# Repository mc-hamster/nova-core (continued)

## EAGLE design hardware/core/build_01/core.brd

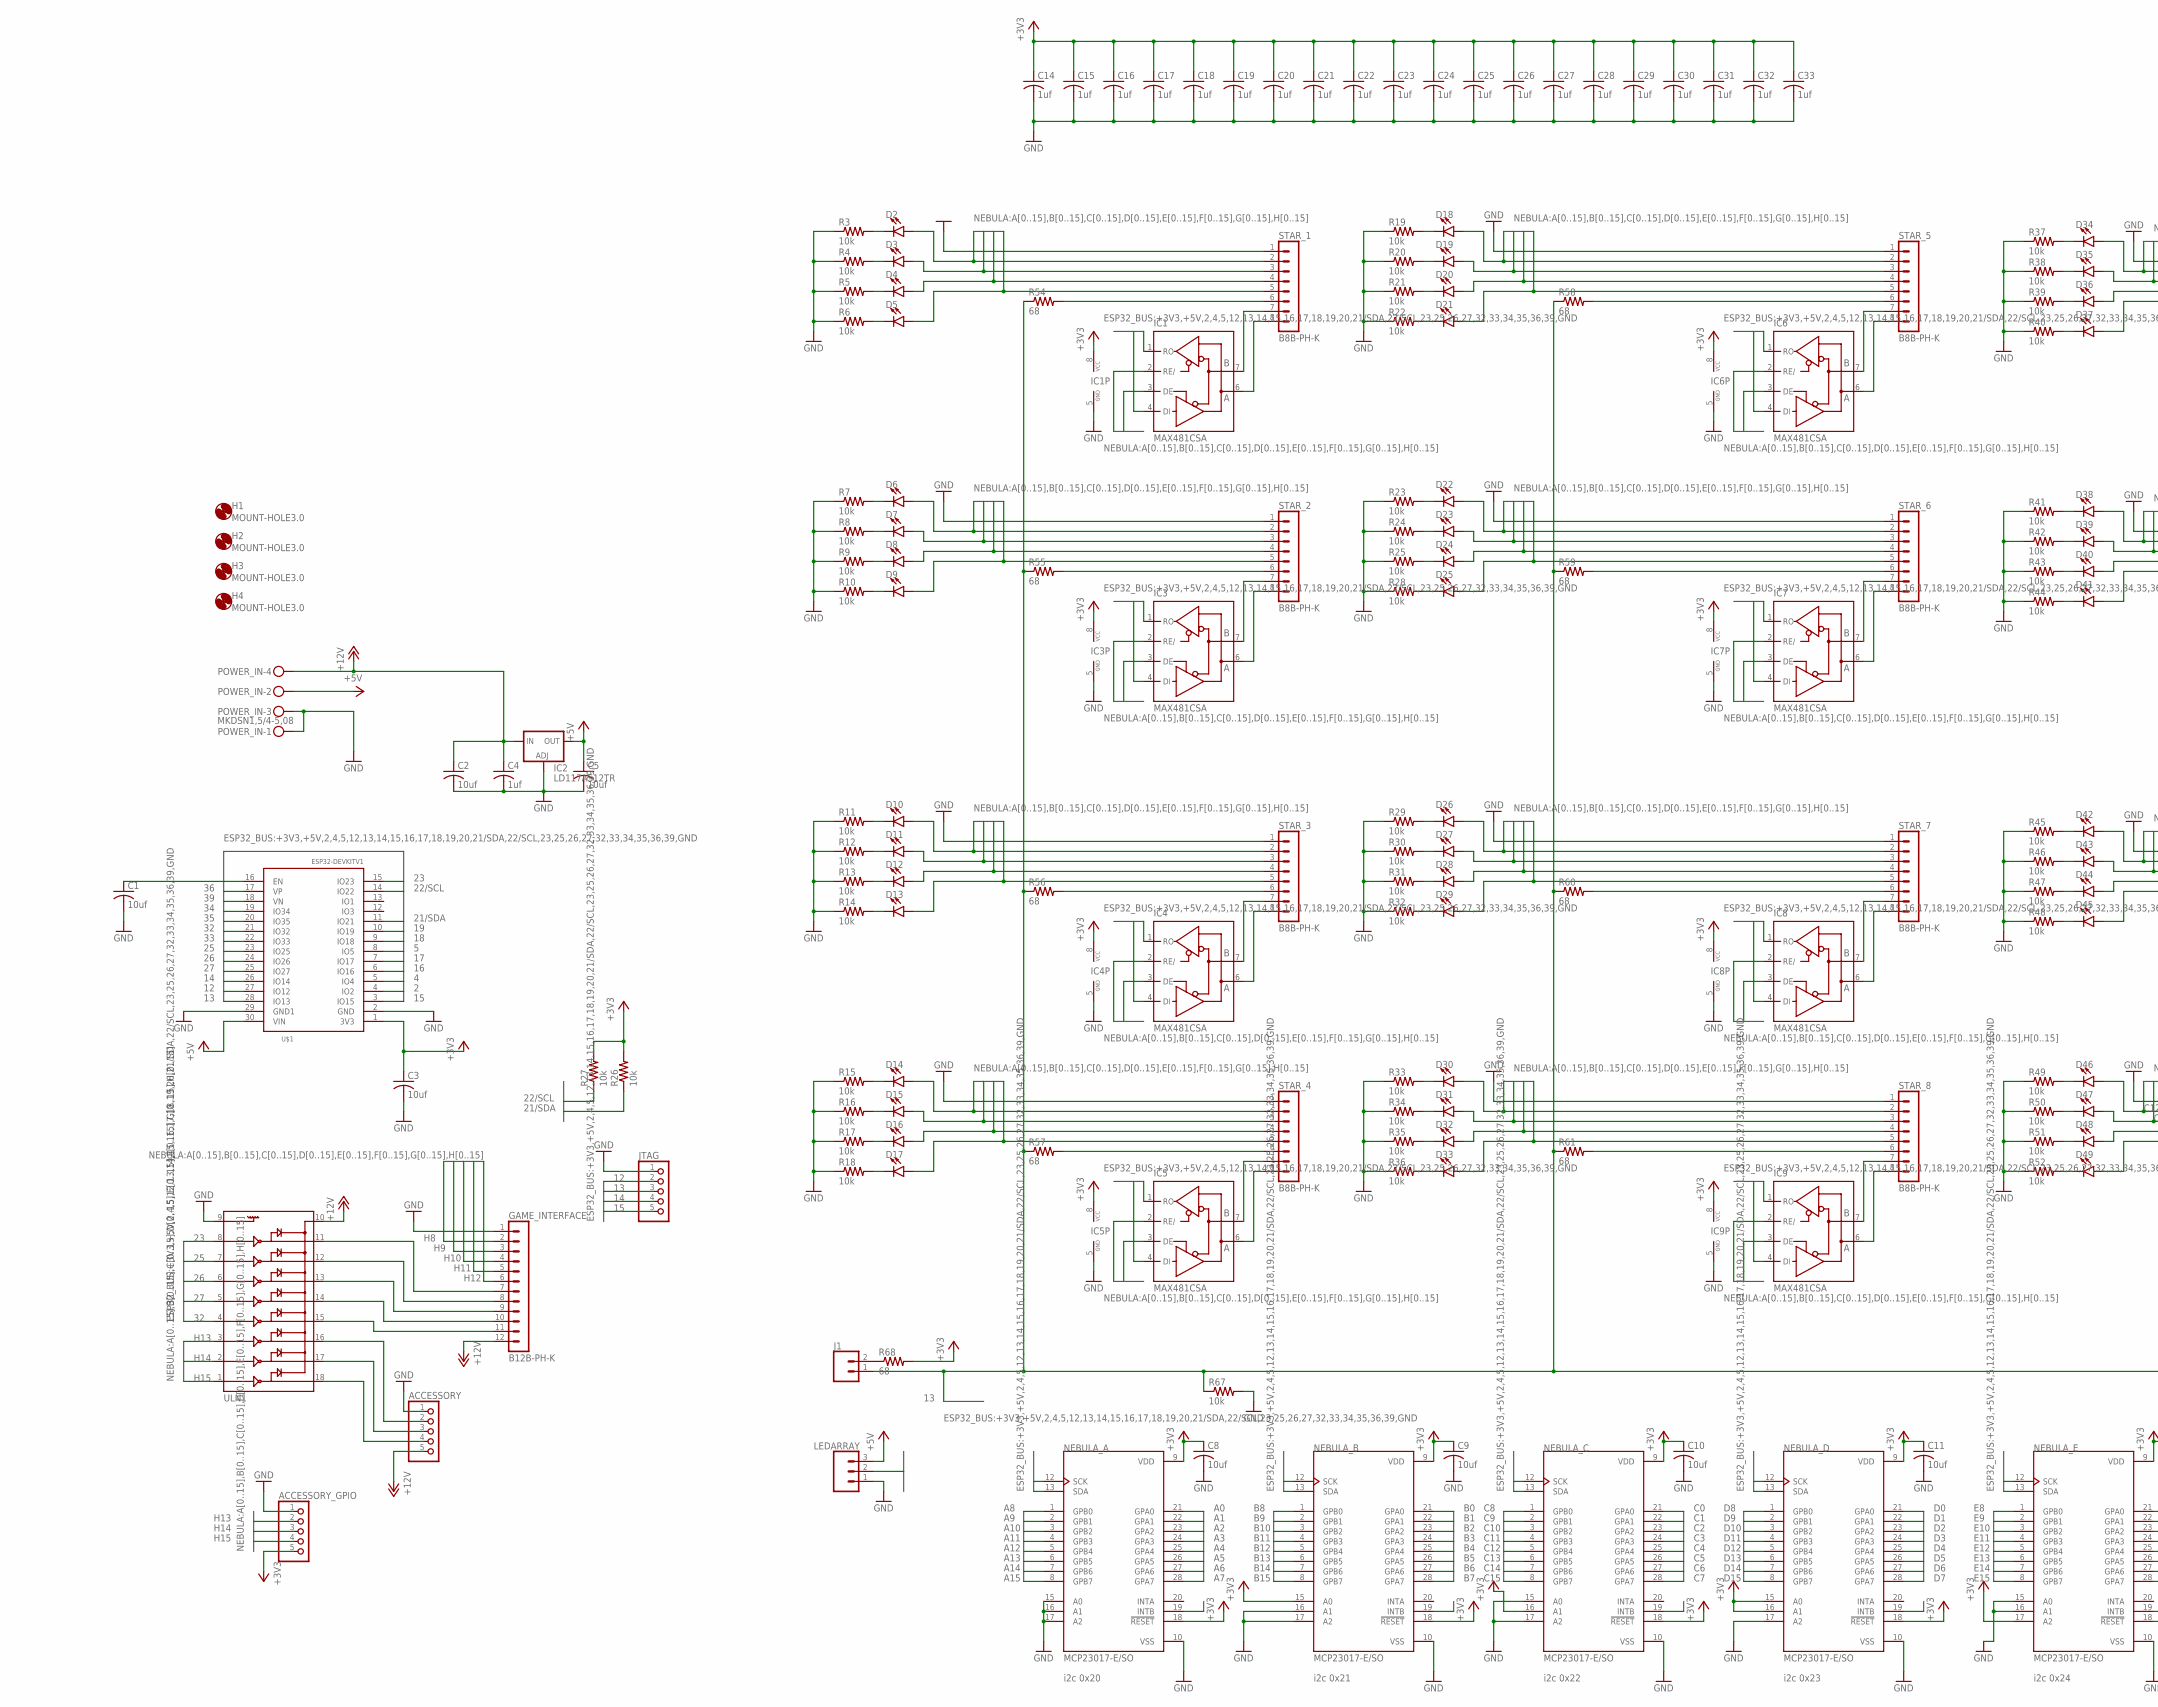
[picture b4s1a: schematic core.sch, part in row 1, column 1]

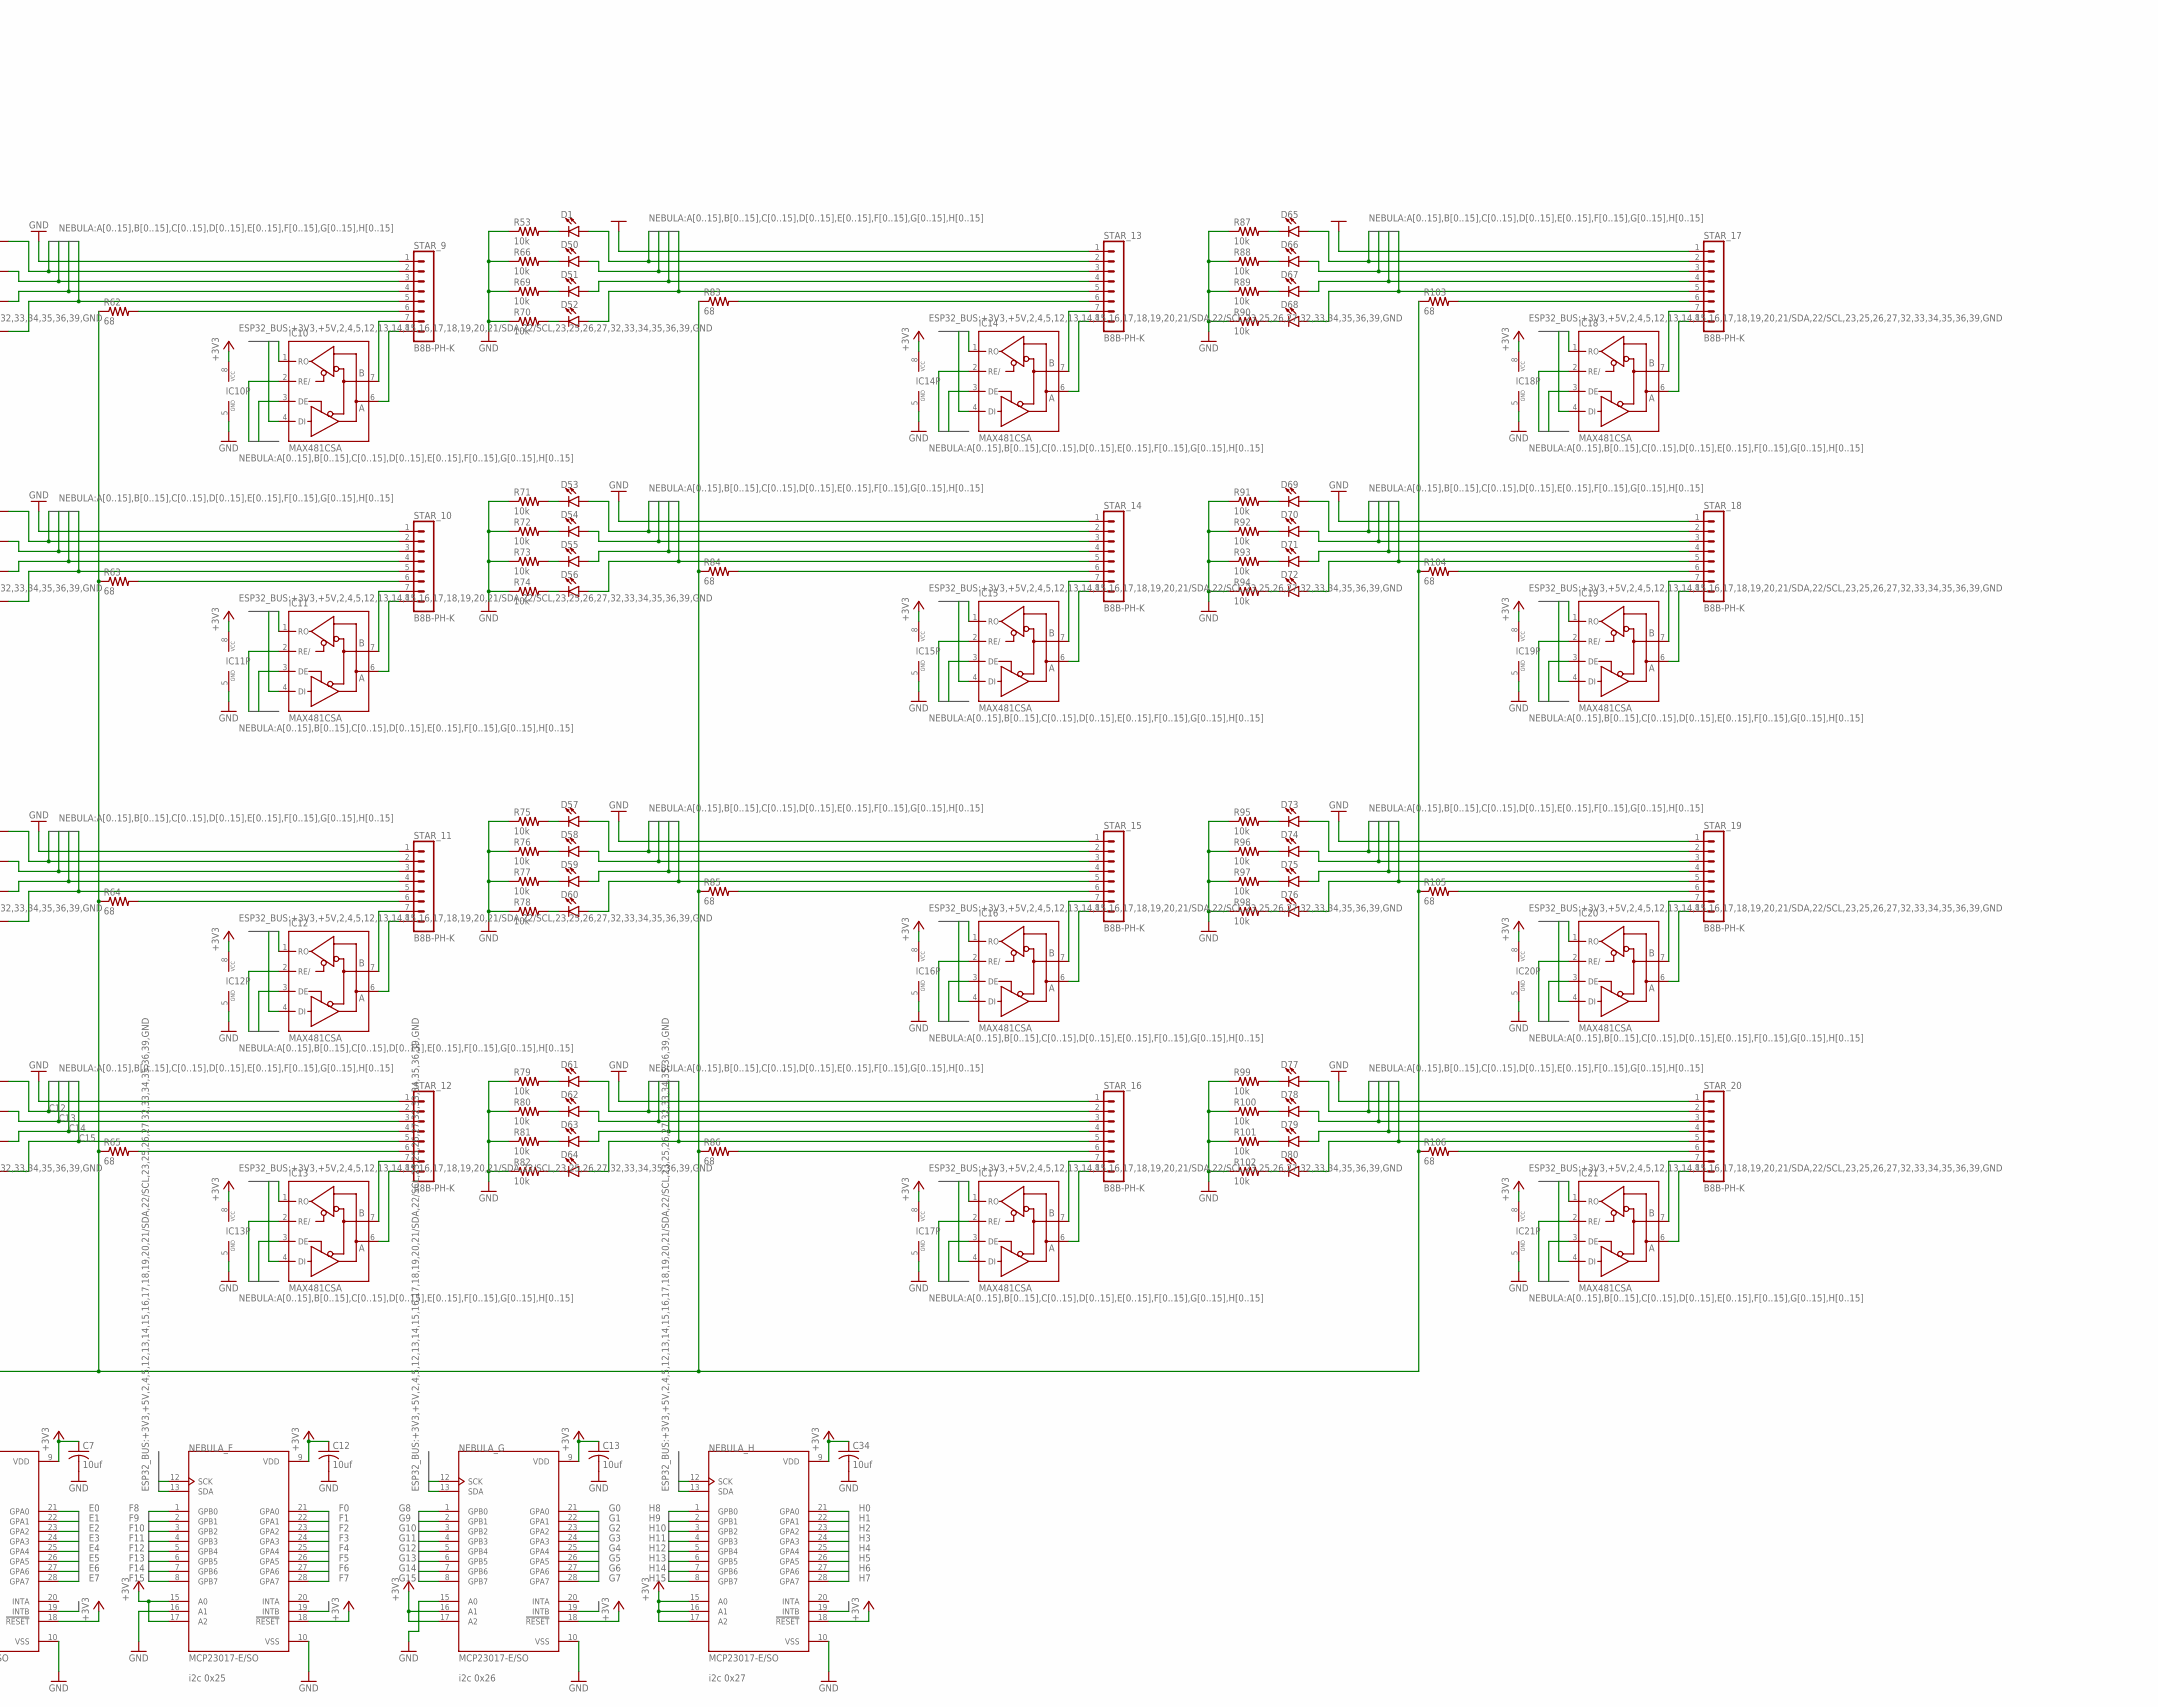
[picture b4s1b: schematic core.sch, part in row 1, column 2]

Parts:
ACCESSORY: PINHD-1X5; 1X05
ACCESSORY_GPIO: PINHD-1X5; 1X05
C1, C2, C3, C5, C7, C8, C9, C10, C11, C12, C13, C34: 10uf; C0603; LCSC_PART C19702
C4, C14, C15, C16, C17, C18, C19, C20, C21, C22, C23, C24, C25, C26, C27, C28, C29, C30, C31, C32, C33: 1uf; C0805; LCSC_PART C15849
D1, D2, D6, D10, D14, D18, D22, D26, D30, D34, D38, D42, D46, D53, D57, D61, D65, D69, D73, D77: LED0603; LED-0603; LCSC_PART C2286
D3, D7, D11, D15, D19, D23, D27, D31, D35, D39, D43, D47, D50, D54, D58, D62, D66, D70, D74, D78: LED0603; LED-0603; LCSC_PART C72043
D4, D8, D12, D16, D20, D24, D28, D32, D36, D40, D44, D48, D51, D55, D59, D63, D67, D71, D75, D79: LED0603; LED-0603; LCSC_PART C72041
D5, D9, D13, D17, D21, D25, D29, D33, D37, D41, D45, D49, D52, D56, D60, D64, D68, D72, D76, D80: LED0603; LED-0603; LCSC_PART C2290
GAME_INTERFACE: B12B-PH-K
H1, H2, H3, H4: MOUNT-HOLE3.0; 3,0
IC1, IC3, IC4, IC5, IC6, IC7, IC8, IC9, IC10, IC11, IC12, IC13, IC14, IC15, IC16, IC17, IC18, IC19, IC20, IC21: MAX481CSA; SO08; LCSC_PART C8963
IC2: LD117AS12TR; SOT223; LCSC_PART C6187
J1: CONN_02JST-PTH-2; JST-2-PTH
JTAG: PINHD-1X5; 1X05
LEDARRAY: CONN_03; 1X03
NEBULA_A: MCP23017-E/SO; SOIC127P1030X265-28N; LCSC_PART C629440
NEBULA_B: MCP23017-E/SO; SOIC127P1030X265-28N; LCSC_PART C629440
NEBULA_C: MCP23017-E/SO; SOIC127P1030X265-28N; LCSC_PART C629440
NEBULA_D: MCP23017-E/SO; SOIC127P1030X265-28N; LCSC_PART C629440
NEBULA_E: MCP23017-E/SO; SOIC127P1030X265-28N; LCSC_PART C629440
NEBULA_F: MCP23017-E/SO; SOIC127P1030X265-28N; LCSC_PART C629440
NEBULA_G: MCP23017-E/SO; SOIC127P1030X265-28N; LCSC_PART C629440
NEBULA_H: MCP23017-E/SO; SOIC127P1030X265-28N; LCSC_PART C629440
POWER_IN: MKDSN1,5/4-5,08
R3, R4, R5, R6, R7, R8, R9, R10, R11, R12, R13, R14, R15, R16, R17, R18, R19, R20, R21, R22, R23, R24, R25, R26, R27, R28, R29, R30, R31, R32, R33, R34, R35, R36, R37, R38, R39, R40, R41, R42, R43, R44, R45, R46, R47, R48, R49, R50, R51, R52, R53, R66, R67, R69, R70, R71, R72, R73, R74, R75, R76, R77, R78, R79, R80, R81, R82, R87, R88, R89, R90, R91, R92, R93, R94, R95, R96, R97, R98, R99, R100, R101, R102: 10k; R0603; LCSC_PART C25804
R54, R55, R56, R57, R58, R59, R60, R61, R62, R63, R64, R65, R68, R83, R84, R85, R86, R103, R104, R105, R106: 68; R0603; LCSC_PART C25804
STAR_1, STAR_2, STAR_3, STAR_4, STAR_5, STAR_6, STAR_7, STAR_8, STAR_9, STAR_10, STAR_11, STAR_12, STAR_13, STAR_14, STAR_15, STAR_16, STAR_17, STAR_18, STAR_19, STAR_20: B8B-PH-K
U$1: ESP32DEVKITV1; ESP32-DEVKITV1
ULN1: ULN2803SOIC; SO018

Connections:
2: U$1.4 (IO2)
4: LEDARRAY.2, U$1.5 (IO4)
5: U$1.8 (IO5)
12: JTAG.2, U$1.27 (IO12)
13: J1.1, JTAG.3, R54.1, R55.1, R56.1, R57.1, R58.1, R59.1, R60.1, R61.1, R62.1, R63.1, R64.1, R65.1, R67.1, R83.1, R84.1, R85.1, R86.1, R103.1, R104.1, R105.1, R106.1, U$1.28 (IO13)
14: JTAG.4, U$1.26 (IO14)
15: JTAG.5, U$1.3 (IO15)
16: IC1.1 (RO), IC3.1 (RO), IC4.1 (RO), IC5.1 (RO), IC6.1 (RO), IC7.1 (RO), IC8.1 (RO), IC9.1 (RO), IC10.1 (RO), IC11.1 (RO), IC12.1 (RO), IC13.1 (RO), IC14.1 (RO), IC15.1 (RO), IC16.1 (RO), IC17.1 (RO), IC18.1 (RO), IC19.1 (RO), IC20.1 (RO), IC21.1 (RO), U$1.6 (IO16)
17: IC1.4 (DI), IC3.4 (DI), IC4.4 (DI), IC5.4 (DI), IC6.4 (DI), IC7.4 (DI), IC8.4 (DI), IC9.4 (DI), IC10.4 (DI), IC11.4 (DI), IC12.4 (DI), IC13.4 (DI), IC14.4 (DI), IC15.4 (DI), IC16.4 (DI), IC17.4 (DI), IC18.4 (DI), IC19.4 (DI), IC20.4 (DI), IC21.4 (DI), U$1.7 (IO17)
18: NEBULA_E.19 (INTB), U$1.9 (IO18)
19: NEBULA_F.19 (INTB), U$1.10 (IO19)
21/SDA: NEBULA_A.13 (SDA), NEBULA_B.13 (SDA), NEBULA_C.13 (SDA), NEBULA_D.13 (SDA), NEBULA_E.13 (SDA), NEBULA_F.13 (SDA), NEBULA_G.13 (SDA), NEBULA_H.13 (SDA), R26.1, U$1.11 (IO21)
22/SCL: NEBULA_A.12 (SCK), NEBULA_B.12 (SCK), NEBULA_C.12 (SCK), NEBULA_D.12 (SCK), NEBULA_E.12 (SCK), NEBULA_F.12 (SCK), NEBULA_G.12 (SCK), NEBULA_H.12 (SCK), R27.1, U$1.14 (IO22)
23: U$1.15 (IO23), ULN1.8
25: U$1.23 (IO25), ULN1.7
26: U$1.24 (IO26), ULN1.6
27: U$1.25 (IO27), ULN1.5
32: U$1.21 (IO32), ULN1.4
33: NEBULA_G.19 (INTB), NEBULA_H.19 (INTB), U$1.22 (IO33)
34: NEBULA_A.19 (INTB), U$1.19 (IO34)
35: NEBULA_B.19 (INTB), U$1.20 (IO35)
36: NEBULA_C.19 (INTB), U$1.17 (VP)
39: NEBULA_D.19 (INTB), U$1.18 (VN)
+3V3: ACCESSORY_GPIO.5, C3.1, C7.1, C8.1, C9.1, C10.1, C11.1, C12.1, C13.1, C14.1, C15.1, C16.1, C17.1, C18.1, C19.1, C20.1, C21.1, C22.1, C23.1, C24.1, C25.1, C26.1, C27.1, C28.1, C29.1, C30.1, C31.1, C32.1, C33.1, C34.1, IC1.8 (VCC), IC3.8 (VCC), IC4.8 (VCC), IC5.8 (VCC), IC6.8 (VCC), IC7.8 (VCC), IC8.8 (VCC), IC9.8 (VCC), IC10.8 (VCC), IC11.8 (VCC), IC12.8 (VCC), IC13.8 (VCC), IC14.8 (VCC), IC15.8 (VCC), IC16.8 (VCC), IC17.8 (VCC), IC18.8 (VCC), IC19.8 (VCC), IC20.8 (VCC), IC21.8 (VCC), NEBULA_A.9 (VDD), NEBULA_A.18 (!RESET), NEBULA_B.9 (VDD), NEBULA_B.15 (A0), NEBULA_B.18 (!RESET), NEBULA_C.9 (VDD), NEBULA_C.16 (A1), NEBULA_C.18 (!RESET), NEBULA_D.9 (VDD), NEBULA_D.15 (A0), NEBULA_D.16 (A1), NEBULA_D.18 (!RESET), NEBULA_E.9 (VDD), NEBULA_E.17 (A2), NEBULA_E.18 (!RESET), NEBULA_F.9 (VDD), NEBULA_F.15 (A0), NEBULA_F.17 (A2), NEBULA_F.18 (!RESET), NEBULA_G.9 (VDD), NEBULA_G.16 (A1), NEBULA_G.17 (A2), NEBULA_G.18 (!RESET), NEBULA_H.9 (VDD), NEBULA_H.15 (A0), NEBULA_H.16 (A1), NEBULA_H.17 (A2), NEBULA_H.18 (!RESET), R26.2, R27.2, R68.2, U$1.1 (3V3)
+5V: C5.1, IC2.4 (OUT), LEDARRAY.3, POWER_IN.2, U$1.30 (VIN)
+12V: ACCESSORY.5, C2.1, C4.1, GAME_INTERFACE.12, IC2.3 (IN), POWER_IN.4, ULN1.10
A0: D2.A, NEBULA_A.21 (GPA0), STAR_1.2
A1: D3.A, NEBULA_A.22 (GPA1), STAR_1.3
A2: D4.A, NEBULA_A.23 (GPA2), STAR_1.4
A3: D5.A, NEBULA_A.24 (GPA3), STAR_1.5
A4: D6.A, NEBULA_A.25 (GPA4), STAR_2.2
A5: D7.A, NEBULA_A.26 (GPA5), STAR_2.3
A6: D8.A, NEBULA_A.27 (GPA6), STAR_2.4
A7: D9.A, NEBULA_A.28 (GPA7), STAR_2.5
A8: D10.A, NEBULA_A.1 (GPB0), STAR_3.2
A9: D11.A, NEBULA_A.2 (GPB1), STAR_3.3
A10: D12.A, NEBULA_A.3 (GPB2), STAR_3.4
A11: D13.A, NEBULA_A.4 (GPB3), STAR_3.5
A12: D14.A, NEBULA_A.5 (GPB4), STAR_4.2
A13: D15.A, NEBULA_A.6 (GPB5), STAR_4.3
A14: D16.A, NEBULA_A.7 (GPB6), STAR_4.4
A15: D17.A, NEBULA_A.8 (GPB7), STAR_4.5
B0: D18.A, NEBULA_B.21 (GPA0), STAR_5.2
B1: D19.A, NEBULA_B.22 (GPA1), STAR_5.3
B2: D20.A, NEBULA_B.23 (GPA2), STAR_5.4
B3: D21.A, NEBULA_B.24 (GPA3), STAR_5.5
B4: D22.A, NEBULA_B.25 (GPA4), STAR_6.2
B5: D23.A, NEBULA_B.26 (GPA5), STAR_6.3
B6: D24.A, NEBULA_B.27 (GPA6), STAR_6.4
B7: D25.A, NEBULA_B.28 (GPA7), STAR_6.5
B8: D26.A, NEBULA_B.1 (GPB0), STAR_7.2
B9: D27.A, NEBULA_B.2 (GPB1), STAR_7.3
B10: D28.A, NEBULA_B.3 (GPB2), STAR_7.4
B11: D29.A, NEBULA_B.4 (GPB3), STAR_7.5
B12: D30.A, NEBULA_B.5 (GPB4), STAR_8.2
B13: D31.A, NEBULA_B.6 (GPB5), STAR_8.3
B14: D32.A, NEBULA_B.7 (GPB6), STAR_8.4
B15: D33.A, NEBULA_B.8 (GPB7), STAR_8.5
C0: D34.A, NEBULA_C.21 (GPA0), STAR_9.2
C1: D35.A, NEBULA_C.22 (GPA1), STAR_9.3
C2: D36.A, NEBULA_C.23 (GPA2), STAR_9.4
C3: D37.A, NEBULA_C.24 (GPA3), STAR_9.5
C4: D38.A, NEBULA_C.25 (GPA4), STAR_10.2
C5: D39.A, NEBULA_C.26 (GPA5), STAR_10.3
C6: D40.A, NEBULA_C.27 (GPA6), STAR_10.4
C7: D41.A, NEBULA_C.28 (GPA7), STAR_10.5
C8: D42.A, NEBULA_C.1 (GPB0), STAR_11.2
C9: D43.A, NEBULA_C.2 (GPB1), STAR_11.3
C10: D44.A, NEBULA_C.3 (GPB2), STAR_11.4
C11: D45.A, NEBULA_C.4 (GPB3), STAR_11.5
C12: D46.A, NEBULA_C.5 (GPB4), STAR_12.2
C13: D47.A, NEBULA_C.6 (GPB5), STAR_12.3
C14: D48.A, NEBULA_C.7 (GPB6), STAR_12.4
C15: D49.A, NEBULA_C.8 (GPB7), STAR_12.5
D0: D1.A, NEBULA_D.21 (GPA0), STAR_13.2
D1: D50.A, NEBULA_D.22 (GPA1), STAR_13.3
D2: D51.A, NEBULA_D.23 (GPA2), STAR_13.4
D3: D52.A, NEBULA_D.24 (GPA3), STAR_13.5
D4: D53.A, NEBULA_D.25 (GPA4), STAR_14.2
D5: D54.A, NEBULA_D.26 (GPA5), STAR_14.3
D6: D55.A, NEBULA_D.27 (GPA6), STAR_14.4
D7: D56.A, NEBULA_D.28 (GPA7), STAR_14.5
D8: D57.A, NEBULA_D.1 (GPB0), STAR_15.2
D9: D58.A, NEBULA_D.2 (GPB1), STAR_15.3
D10: D59.A, NEBULA_D.3 (GPB2), STAR_15.4
D11: D60.A, NEBULA_D.4 (GPB3), STAR_15.5
D12: D61.A, NEBULA_D.5 (GPB4), STAR_16.2
D13: D62.A, NEBULA_D.6 (GPB5), STAR_16.3
D14: D63.A, NEBULA_D.7 (GPB6), STAR_16.4
D15: D64.A, NEBULA_D.8 (GPB7), STAR_16.5
E0: D65.A, NEBULA_E.21 (GPA0), STAR_17.2
E1: D66.A, NEBULA_E.22 (GPA1), STAR_17.3
E2: D67.A, NEBULA_E.23 (GPA2), STAR_17.4
E3: D68.A, NEBULA_E.24 (GPA3), STAR_17.5
E4: D69.A, NEBULA_E.25 (GPA4), STAR_18.2
E5: D70.A, NEBULA_E.26 (GPA5), STAR_18.3
E6: D71.A, NEBULA_E.27 (GPA6), STAR_18.4
E7: D72.A, NEBULA_E.28 (GPA7), STAR_18.5
E8: D73.A, NEBULA_E.1 (GPB0), STAR_19.2
E9: D74.A, NEBULA_E.2 (GPB1), STAR_19.3
E10: D75.A, NEBULA_E.3 (GPB2), STAR_19.4
E11: D76.A, NEBULA_E.4 (GPB3), STAR_19.5
E12: D77.A, NEBULA_E.5 (GPB4), STAR_20.2
E13: D78.A, NEBULA_E.6 (GPB5), STAR_20.3
E14: D79.A, NEBULA_E.7 (GPB6), STAR_20.4
E15: D80.A, NEBULA_E.8 (GPB7), STAR_20.5
F0: IC1.2 (RE/), NEBULA_F.21 (GPA0)
F1: IC1.3 (DE), NEBULA_F.22 (GPA1)
F2: IC3.2 (RE/), NEBULA_F.23 (GPA2)
F3: IC3.3 (DE), NEBULA_F.24 (GPA3)
F4: IC4.2 (RE/), NEBULA_F.25 (GPA4)
F5: IC4.3 (DE), NEBULA_F.26 (GPA5)
F6: IC5.2 (RE/), NEBULA_F.27 (GPA6)
F7: IC5.3 (DE), NEBULA_F.28 (GPA7)
F8: IC6.2 (RE/), NEBULA_F.1 (GPB0)
F9: IC6.3 (DE), NEBULA_F.2 (GPB1)
F10: IC7.2 (RE/), NEBULA_F.3 (GPB2)
F11: IC7.3 (DE), NEBULA_F.4 (GPB3)
F12: IC8.2 (RE/), NEBULA_F.5 (GPB4)
F13: IC8.3 (DE), NEBULA_F.6 (GPB5)
F14: IC9.2 (RE/), NEBULA_F.7 (GPB6)
F15: IC9.3 (DE), NEBULA_F.8 (GPB7)
G0: IC10.2 (RE/), NEBULA_G.21 (GPA0)
G1: IC10.3 (DE), NEBULA_G.22 (GPA1)
G2: IC11.2 (RE/), NEBULA_G.23 (GPA2)
G3: IC11.3 (DE), NEBULA_G.24 (GPA3)
G4: IC12.2 (RE/), NEBULA_G.25 (GPA4)
G5: IC12.3 (DE), NEBULA_G.26 (GPA5)
G6: IC13.2 (RE/), NEBULA_G.27 (GPA6)
G7: IC13.3 (DE), NEBULA_G.28 (GPA7)
G8: IC14.2 (RE/), NEBULA_G.1 (GPB0)
G9: IC14.3 (DE), NEBULA_G.2 (GPB1)
G10: IC15.2 (RE/), NEBULA_G.3 (GPB2)
G11: IC15.3 (DE), NEBULA_G.4 (GPB3)
G12: IC16.2 (RE/), NEBULA_G.5 (GPB4)
G13: IC16.3 (DE), NEBULA_G.6 (GPB5)
G14: IC17.2 (RE/), NEBULA_G.7 (GPB6)
G15: IC17.3 (DE), NEBULA_G.8 (GPB7)
GND: ACCESSORY.1, ACCESSORY_GPIO.1, C1.2, C2.2, C3.2, C4.2, C5.2, C7.2, C8.2, C9.2, C10.2, C11.2, C12.2, C13.2, C14.2, C15.2, C16.2, C17.2, C18.2, C19.2, C20.2, C21.2, C22.2, C23.2, C24.2, C25.2, C26.2, C27.2, C28.2, C29.2, C30.2, C31.2, C32.2, C33.2, C34.2, GAME_INTERFACE.1, IC1.5 (GND), IC2.1 (ADJ), IC3.5 (GND), IC4.5 (GND), IC5.5 (GND), IC6.5 (GND), IC7.5 (GND), IC8.5 (GND), IC9.5 (GND), IC10.5 (GND), IC11.5 (GND), IC12.5 (GND), IC13.5 (GND), IC14.5 (GND), IC15.5 (GND), IC16.5 (GND), IC17.5 (GND), IC18.5 (GND), IC19.5 (GND), IC20.5 (GND), IC21.5 (GND), JTAG.1, LEDARRAY.1, NEBULA_A.10 (VSS), NEBULA_A.15 (A0), NEBULA_A.16 (A1), NEBULA_A.17 (A2), NEBULA_B.10 (VSS), NEBULA_B.16 (A1), NEBULA_B.17 (A2), NEBULA_C.10 (VSS), NEBULA_C.15 (A0), NEBULA_C.17 (A2), NEBULA_D.10 (VSS), NEBULA_D.17 (A2), NEBULA_E.10 (VSS), NEBULA_E.15 (A0), NEBULA_E.16 (A1), NEBULA_F.10 (VSS), NEBULA_F.16 (A1), NEBULA_G.10 (VSS), NEBULA_G.15 (A0), NEBULA_H.10 (VSS), POWER_IN.1, POWER_IN.3, R3.1, R4.1, R5.1, R6.1, R7.1, R8.1, R9.1, R10.1, R11.1, R12.1, R13.1, R14.1, R15.1, R16.1, R17.1, R18.1, R19.1, R20.1, R21.1, R22.1, R23.1, R24.1, R25.1, R28.1, R29.1, R30.1, R31.1, R32.1, R33.1, R34.1, R35.1, R36.1, R37.1, R38.1, R39.1, R40.1, R41.1, R42.1, R43.1, R44.1, R45.1, R46.1, R47.1, R48.1, R49.1, R50.1, R51.1, R52.1, R53.1, R66.1, R67.2, R69.1, R70.1, R71.1, R72.1, R73.1, R74.1, R75.1, R76.1, R77.1, R78.1, R79.1, R80.1, R81.1, R82.1, R87.1, R88.1, R89.1, R90.1, R91.1, R92.1, R93.1, R94.1, R95.1, R96.1, R97.1, R98.1, R99.1, R100.1, R101.1, R102.1, STAR_1.1, STAR_2.1, STAR_3.1, STAR_4.1, STAR_5.1, STAR_6.1, STAR_7.1, STAR_8.1, STAR_9.1, STAR_10.1, STAR_11.1, STAR_12.1, STAR_13.1, STAR_14.1, STAR_15.1, STAR_16.1, STAR_17.1, STAR_18.1, STAR_19.1, STAR_20.1, U$1.2 (GND), U$1.29 (GND1), ULN1.9
H0: IC18.2 (RE/), NEBULA_H.21 (GPA0)
H1: IC18.3 (DE), NEBULA_H.22 (GPA1)
H2: IC19.2 (RE/), NEBULA_H.23 (GPA2)
H3: IC19.3 (DE), NEBULA_H.24 (GPA3)
H4: IC20.2 (RE/), NEBULA_H.25 (GPA4)
H5: IC20.3 (DE), NEBULA_H.26 (GPA5)
H6: IC21.2 (RE/), NEBULA_H.27 (GPA6)
H7: IC21.3 (DE), NEBULA_H.28 (GPA7)
H8: GAME_INTERFACE.2, NEBULA_H.1 (GPB0)
H9: GAME_INTERFACE.3, NEBULA_H.2 (GPB1)
H10: GAME_INTERFACE.4, NEBULA_H.3 (GPB2)
H11: GAME_INTERFACE.5, NEBULA_H.4 (GPB3)
H12: GAME_INTERFACE.6, NEBULA_H.5 (GPB4)
H13: ACCESSORY_GPIO.2, NEBULA_H.6 (GPB5), ULN1.3
H14: ACCESSORY_GPIO.3, NEBULA_H.7 (GPB6), ULN1.2
H15: ACCESSORY_GPIO.4, NEBULA_H.8 (GPB7), ULN1.1
unnamed: C1.1, U$1.16 (EN)
unnamed: R55.2, STAR_2.6
unnamed: D2.C, R3.2
unnamed: D3.C, R4.2
unnamed: D4.C, R5.2
unnamed: D5.C, R6.2
unnamed: R56.2, STAR_3.6
unnamed: R57.2, STAR_4.6
unnamed: R54.2, STAR_1.6
unnamed: R58.2, STAR_5.6
unnamed: D6.C, R7.2
unnamed: D7.C, R8.2
unnamed: D8.C, R9.2
unnamed: D9.C, R10.2
unnamed: R59.2, STAR_6.6
unnamed: R60.2, STAR_7.6
unnamed: R61.2, STAR_8.6
unnamed: R65.2, STAR_12.6
unnamed: R64.2, STAR_11.6
unnamed: D10.C, R11.2
unnamed: D11.C, R12.2
unnamed: D12.C, R13.2
unnamed: D13.C, R14.2
unnamed: R63.2, STAR_10.6
unnamed: R62.2, STAR_9.6
unnamed: D1.C, R53.2
unnamed: D50.C, R66.2
unnamed: D14.C, R15.2
unnamed: D15.C, R16.2
unnamed: D16.C, R17.2
unnamed: D17.C, R18.2
unnamed: D51.C, R69.2
unnamed: D52.C, R70.2
unnamed: D65.C, R87.2
unnamed: D53.C, R71.2
unnamed: D18.C, R19.2
unnamed: D19.C, R20.2
unnamed: D20.C, R21.2
unnamed: D21.C, R22.2
unnamed: D54.C, R72.2
unnamed: D55.C, R73.2
unnamed: D56.C, R74.2
unnamed: D57.C, R75.2
unnamed: D22.C, R23.2
unnamed: D23.C, R24.2
unnamed: D24.C, R25.2
unnamed: D25.C, R28.2
unnamed: D58.C, R76.2
unnamed: D59.C, R77.2
unnamed: D60.C, R78.2
unnamed: GAME_INTERFACE.7, ULN1.11
unnamed: D26.C, R29.2
unnamed: D27.C, R30.2
unnamed: D28.C, R31.2
unnamed: D29.C, R32.2
unnamed: GAME_INTERFACE.8, ULN1.12
unnamed: GAME_INTERFACE.9, ULN1.13
unnamed: GAME_INTERFACE.10, ULN1.14
unnamed: GAME_INTERFACE.11, ULN1.15
unnamed: D30.C, R33.2
unnamed: D31.C, R34.2
unnamed: D32.C, R35.2
unnamed: D33.C, R36.2
unnamed: D61.C, R79.2
unnamed: D62.C, R80.2
unnamed: D63.C, R81.2
unnamed: D64.C, R82.2
unnamed: D34.C, R37.2
unnamed: D35.C, R38.2
unnamed: D36.C, R39.2
unnamed: D37.C, R40.2
unnamed: R84.2, STAR_14.6
unnamed: R85.2, STAR_15.6
unnamed: R86.2, STAR_16.6
unnamed: R83.2, STAR_13.6
unnamed: D38.C, R41.2
unnamed: D39.C, R42.2
unnamed: D40.C, R43.2
unnamed: D41.C, R44.2
unnamed: D66.C, R88.2
unnamed: D67.C, R89.2
unnamed: D68.C, R90.2
unnamed: D69.C, R91.2
unnamed: D42.C, R45.2
unnamed: D43.C, R46.2
unnamed: D44.C, R47.2
unnamed: D45.C, R48.2
unnamed: D70.C, R92.2
unnamed: J1.2, R68.1
unnamed: D71.C, R93.2
unnamed: D72.C, R94.2
unnamed: D73.C, R95.2
unnamed: D46.C, R49.2
unnamed: D47.C, R50.2
unnamed: D48.C, R51.2
unnamed: D49.C, R52.2
unnamed: D74.C, R96.2
unnamed: D75.C, R97.2
unnamed: D76.C, R98.2
unnamed: D77.C, R99.2
unnamed: D78.C, R100.2
unnamed: D79.C, R101.2
unnamed: D80.C, R102.2
unnamed: R104.2, STAR_18.6
unnamed: R105.2, STAR_19.6
unnamed: R106.2, STAR_20.6
unnamed: R103.2, STAR_17.6
unnamed: IC1.7 (B), STAR_1.7
unnamed: IC1.6 (A), STAR_1.8
unnamed: IC3.7 (B), STAR_2.7
unnamed: IC3.6 (A), STAR_2.8
unnamed: IC4.7 (B), STAR_3.7
unnamed: IC4.6 (A), STAR_3.8
unnamed: IC5.7 (B), STAR_4.7
unnamed: IC5.6 (A), STAR_4.8
unnamed: IC6.7 (B), STAR_5.7
unnamed: IC6.6 (A), STAR_5.8
unnamed: IC7.7 (B), STAR_6.7
unnamed: IC7.6 (A), STAR_6.8
unnamed: IC8.7 (B), STAR_7.7
unnamed: IC8.6 (A), STAR_7.8
unnamed: IC9.7 (B), STAR_8.7
unnamed: IC9.6 (A), STAR_8.8
unnamed: IC10.7 (B), STAR_9.7
unnamed: IC10.6 (A), STAR_9.8
unnamed: IC11.7 (B), STAR_10.7
unnamed: IC11.6 (A), STAR_10.8
unnamed: IC12.7 (B), STAR_11.7
unnamed: IC12.6 (A), STAR_11.8
unnamed: IC13.7 (B), STAR_12.7
unnamed: IC13.6 (A), STAR_12.8
unnamed: IC14.7 (B), STAR_13.7
unnamed: IC14.6 (A), STAR_13.8
unnamed: IC15.7 (B), STAR_14.7
unnamed: IC15.6 (A), STAR_14.8
unnamed: IC16.7 (B), STAR_15.7
unnamed: IC16.6 (A), STAR_15.8
unnamed: IC17.7 (B), STAR_16.7
unnamed: IC17.6 (A), STAR_16.8
unnamed: IC18.7 (B), STAR_17.7
unnamed: IC18.6 (A), STAR_17.8
unnamed: IC19.7 (B), STAR_18.7
unnamed: IC19.6 (A), STAR_18.8
unnamed: IC20.7 (B), STAR_19.7
unnamed: IC20.6 (A), STAR_19.8
unnamed: IC21.7 (B), STAR_20.7
unnamed: IC21.6 (A), STAR_20.8
unnamed: ACCESSORY.2, ULN1.16
unnamed: ACCESSORY.3, ULN1.17
unnamed: ACCESSORY.4, ULN1.18

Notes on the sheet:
i2c 0x20
i2c 0x21
i2c 0x22
i2c 0x23
i2c 0x24
i2c 0x25
i2c 0x26
i2c 0x27

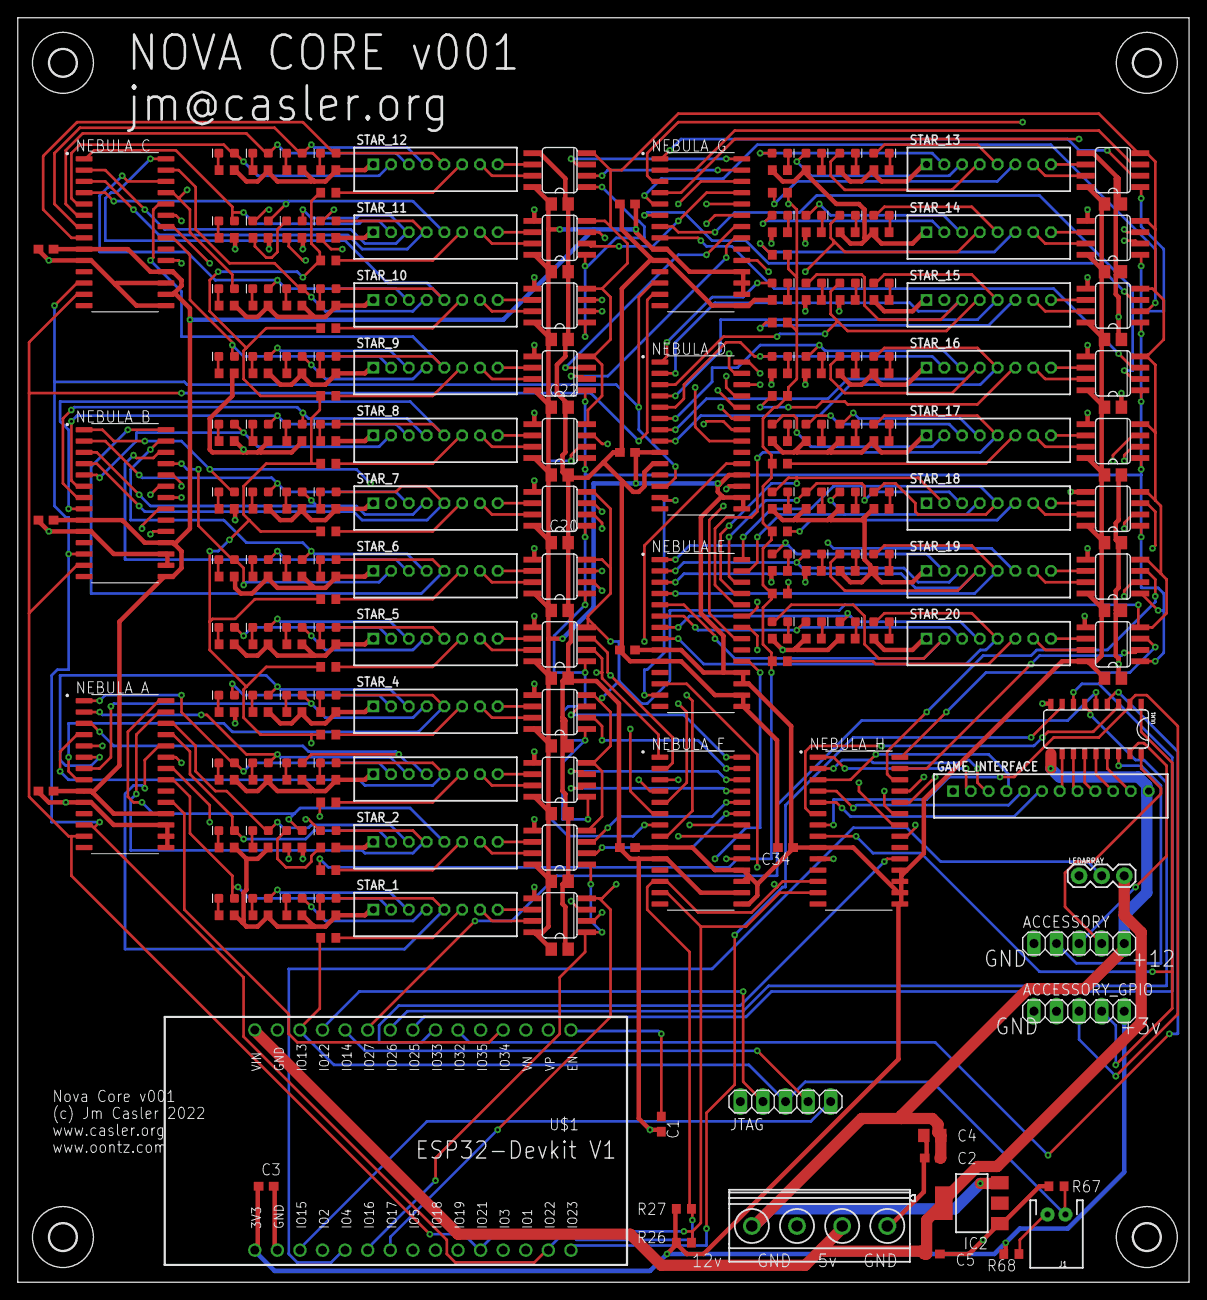
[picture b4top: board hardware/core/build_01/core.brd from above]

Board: 4 copper layers, 131.8 x 142.2 mm, 279 parts (0 on the bottom side), 303 nets.

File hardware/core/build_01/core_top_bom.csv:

Comment,Designator,Footprint,LCSC Part #
1uf,D1 D2 D3 D4 D5 D6 D7 D8 D9 D10 D11 D12 D13 D14 D15 D16 D17 D18 D19 D20 D21 D22 D23 D24 D25 D26 D27 D28 D29 D30 D31 D32 D33 D34 D35 D36 D37 D38 D39 D40 D41 D42 D43 D44 D45 D46 D47 D48 D49 D50 D51 D52 D53 D54 D55 D56 D57 D58 D59 D60 D61 D62 D63 D64 D65 D66 D67 D68 D69 D70 D71 D72 D73 D74 D75 D76 D77 D78 D79 D80 ULN1 C4 C14 C15 C16 C17 C18 C19 C20 C21 C22 C23 C24 C25 C26 C27 C28 C29 C30 C31 C32 C33,C0805,C15849
10k,R3 R4 R5 R6 R7 R8 R9 R10 R11 R12 R13 R14 R15 R16 R17 R18 R19 R20 R21 R22 R23 R24 R25 R26 R27 R28 R29 R30 R31 R32 R33 R34 R35 R36 R37 R38 R39 R40 R41 R42 R43 R44 R45 R46 R47 R48 R49 R50 R51 R52 R53 R66 R67 R69 R70 R71 R72 R73 R74 R75 R76 R77 R78 R79 R80 R81 R82 R87 R88 R89 R90 R91 R92 R93 R94 R95 R96 R97 R98 R99 R100 R101 R102,R0603,C25804
10uf,C1 C2 C3 C5 C7 C8 C9 C10 C11 C12 C13 C34,C0603,C19702
68,R54 R55 R56 R57 R58 R59 R60 R61 R62 R63 R64 R65 R68 R83 R84 R85 R86 R103 R104 R105 R106,R0603,C25804
LD117AS12TR,IC2,SOT223,C6187
MAX481CSA,IC1 IC3 IC4 IC5 IC6 IC7 IC8 IC9 IC10 IC11 IC12 IC13 IC14 IC15 IC16 IC17 IC18 IC19 IC20 IC21,SO08,C8963
MCP23017-E/SO,NEBULA_A NEBULA_B NEBULA_C NEBULA_D NEBULA_E NEBULA_F NEBULA_G NEBULA_H,SOIC127P1030X265-28N,C629440
